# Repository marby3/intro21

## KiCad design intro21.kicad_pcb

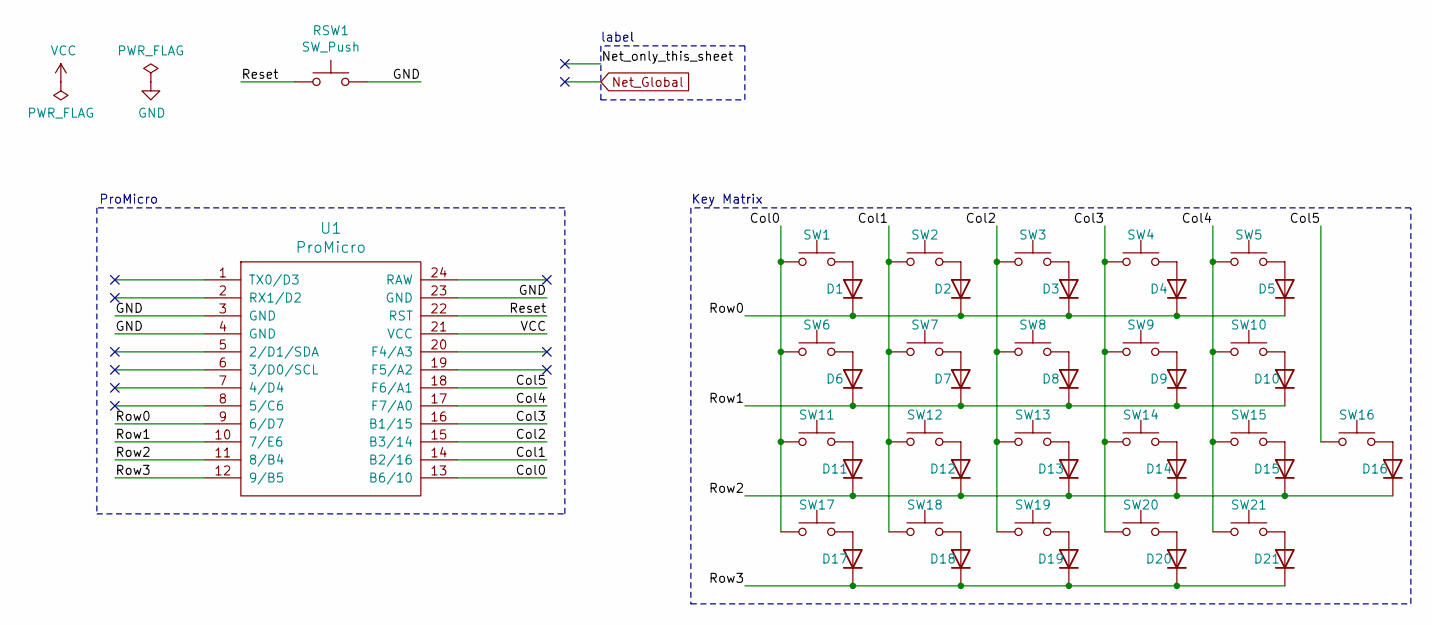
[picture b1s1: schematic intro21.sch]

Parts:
D1, D2, D3, D4, D5, D6, D7, D8, D9, D10, D11, D12, D13, D14, D15, D16, D17, D18, D19, D20, D21: D; D3_TH_SMD
RSW1: SW_Push; ResetSW
SW1, SW2, SW3, SW4, SW5, SW6, SW7, SW8, SW9, SW10, SW11, SW12, SW13, SW14, SW15, SW16, SW17, SW18, SW19, SW20: SW_Push; MXOnly-1U-Hotswap
SW21: SW_Push; MXOnly-2U-Hotswap
U1: ProMicro; ProMicro_v3

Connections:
/Col0: SW1.1, SW6.1, SW11.1, SW17.1, U1.13 (B6/10)
/Col1: SW2.1, SW7.1, SW12.1, SW18.1, U1.14 (B2/16)
/Col2: SW3.1, SW8.1, SW13.1, SW19.1, U1.15 (B3/14)
/Col3: SW4.1, SW9.1, SW14.1, SW20.1, U1.16 (B1/15)
/Col4: SW5.1, SW10.1, SW15.1, SW21.1, U1.17 (F7/A0)
/Col5: SW16.1, U1.18 (F6/A1)
/Reset: RSW1.1, U1.22 (RST)
/Row0: D1.1 (K), D2.1 (K), D3.1 (K), D4.1 (K), D5.1 (K), U1.9 (6/D7)
/Row1: D6.1 (K), D7.1 (K), D8.1 (K), D9.1 (K), D10.1 (K), U1.10 (7/E6)
/Row2: D11.1 (K), D12.1 (K), D13.1 (K), D14.1 (K), D15.1 (K), D16.1 (K), U1.11 (8/B4)
/Row3: D17.1 (K), D18.1 (K), D19.1 (K), D20.1 (K), D21.1 (K), U1.12 (9/B5)
GND: RSW1.2, U1.3 (GND), U1.4 (GND), U1.23 (GND)
unnamed: D1.2 (A), SW1.2
unnamed: D2.2 (A), SW2.2
unnamed: D3.2 (A), SW3.2
unnamed: D4.2 (A), SW4.2
unnamed: D5.2 (A), SW5.2
unnamed: D6.2 (A), SW6.2
unnamed: D7.2 (A), SW7.2
unnamed: D8.2 (A), SW8.2
unnamed: D9.2 (A), SW9.2
unnamed: D10.2 (A), SW10.2
unnamed: D11.2 (A), SW11.2
unnamed: D12.2 (A), SW12.2
unnamed: D13.2 (A), SW13.2
unnamed: D14.2 (A), SW14.2
unnamed: D15.2 (A), SW15.2
unnamed: D16.2 (A), SW16.2
unnamed: D17.2 (A), SW17.2
unnamed: D18.2 (A), SW18.2
unnamed: D19.2 (A), SW19.2
unnamed: D20.2 (A), SW20.2
unnamed: D21.2 (A), SW21.2
VCC: U1.21 (VCC)

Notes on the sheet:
label
Key Matrix
ProMicro

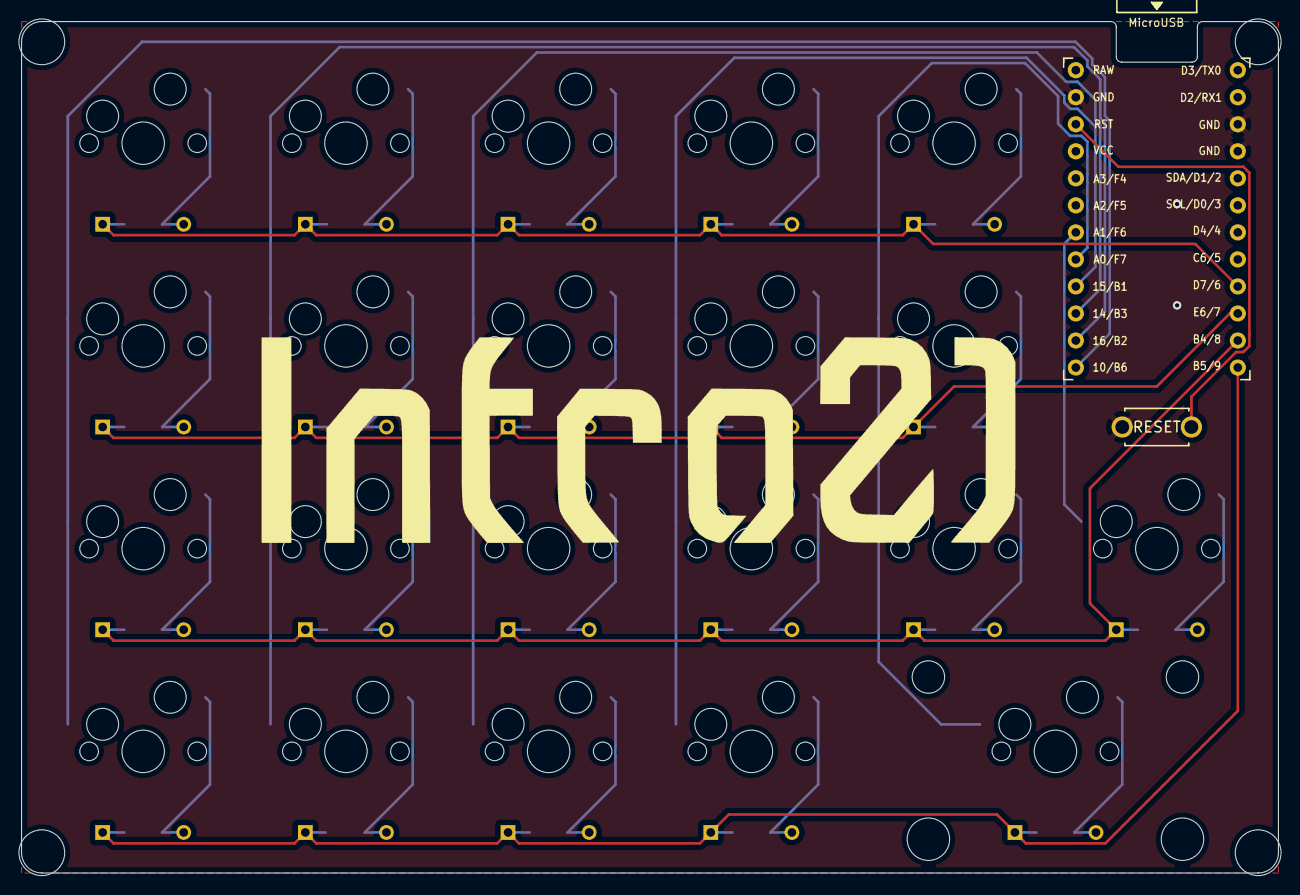
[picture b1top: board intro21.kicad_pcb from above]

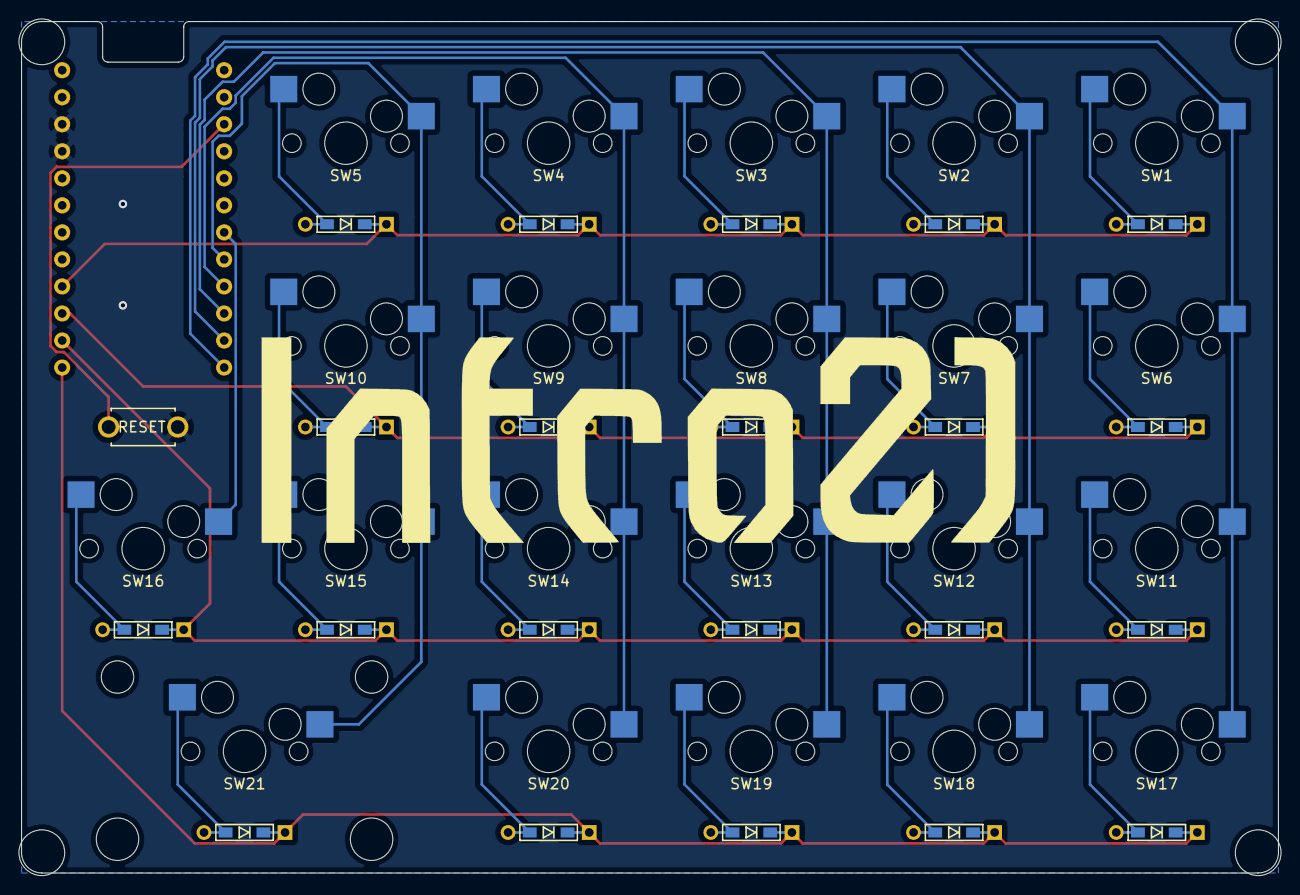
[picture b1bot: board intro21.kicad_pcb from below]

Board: 2 copper layers, 118.1 x 80.0 mm, 48 parts (21 on the bottom side), 33 nets.

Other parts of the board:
Ref**: Val**; spacer_m2
Ref**#2, Ref**#3, Ref**#4: Val**; spacer_m2

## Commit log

2021-05-17 upload
